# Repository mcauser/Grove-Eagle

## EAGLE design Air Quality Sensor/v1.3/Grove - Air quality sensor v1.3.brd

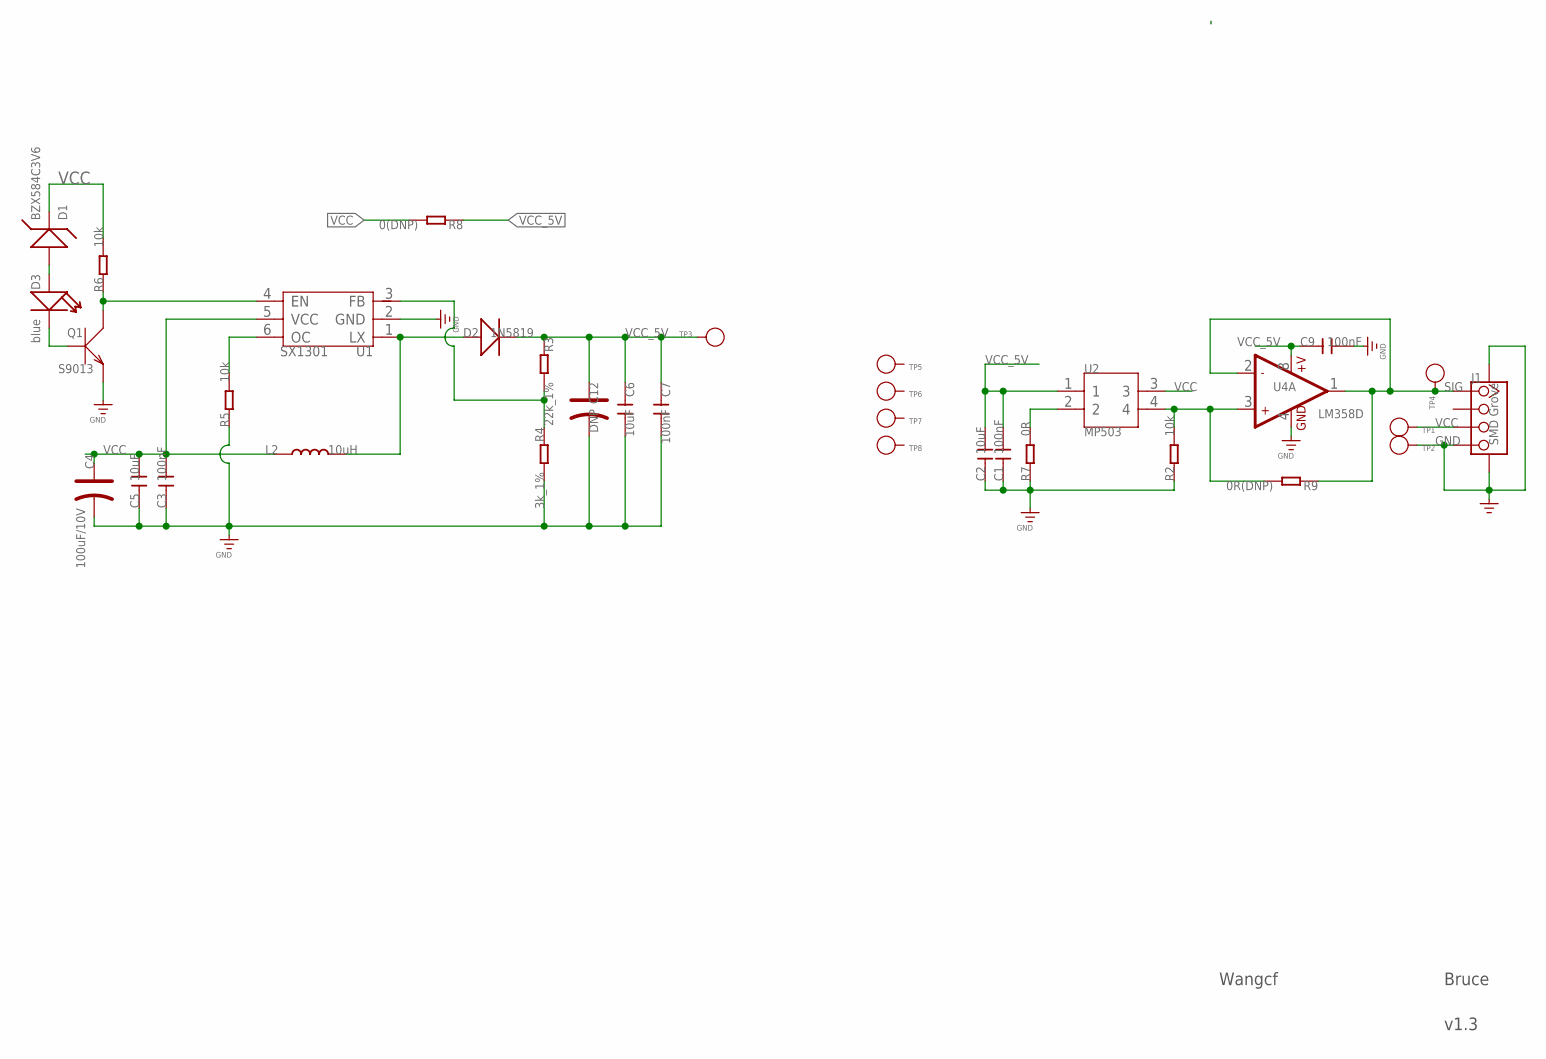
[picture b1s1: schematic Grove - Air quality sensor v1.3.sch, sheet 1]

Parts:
C1, C3, C7, C9: 100nF; C0603
C2, C5, C6: 10uF; C0805
C4: 100uF/10V; AVX-B
C12: DNP; AVX-B
D1: BZX584C3V6; SOD-523
D2: 1N5819; DO-214AC
D3: blue; LED-0603
J1: SMD Grove; 4P-SMD-2.0
L2: 10uH; SD32-4R7MC
Q1: S9013; SOT-23
R2, R5, R6: 10k; R0603
R3: 22k_1%; R0603
R4: 3k_1%; R0603
R7: 0R; R0603
R8: 0(DNP); R0603
R9: 0R(DNP); R0603
TP1, TP2, TP3, TP4, TP5, TP6, TP7, TP8: PAD-TEST-POINT'4545'; TP_4545
U1: SX1301; SOT23-6L
U2: MP503; 4P_3.1_9.4*9.4*17MM
U4: LM358D; SO08

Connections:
EN: Q1.3 (C), R6.1, U1.4 (EN)
GND: C1.1, C2.1, C3.1, C4.-, C5.1, C6.2, C7.2, C9.2, C12.-, J1.4, J1.SS1, J1.SS2, Q1.2 (E), R2.1, R4.2, R5.1, R7.1, TP2.T, U1.2 (GND), U4.4 (GND)
unnamed: R5.2, U1.6 (OC)
unnamed: D1.+, D3.+
unnamed: D2.1 (+), L2.2, U1.1 (LX)
unnamed: D3.-, Q1.1 (B)
unnamed: R7.2, U2.2
unnamed: R3.2, R4.1, U1.3 (FB)
unnamed: R2.2, R9.2, U2.4, U4.3 (+IN1)
SIG: J1.1, R9.1, TP4.T, U4.1 (OUT1), U4.2 (-IN1)
VCC: C3.2, C4.+, C5.2, D1.-, J1.3, L2.1, R6.2, R8.2, TP1.T, U1.5 (VCC), U2.3
VCC_5V: C1.2, C2.2, C6.1, C7.1, C9.1, C12.+, D2.2 (-), R3.1, R8.1, TP3.T, U2.1, U4.8 (+V)

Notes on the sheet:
Wangcf
v1.3
Bruce

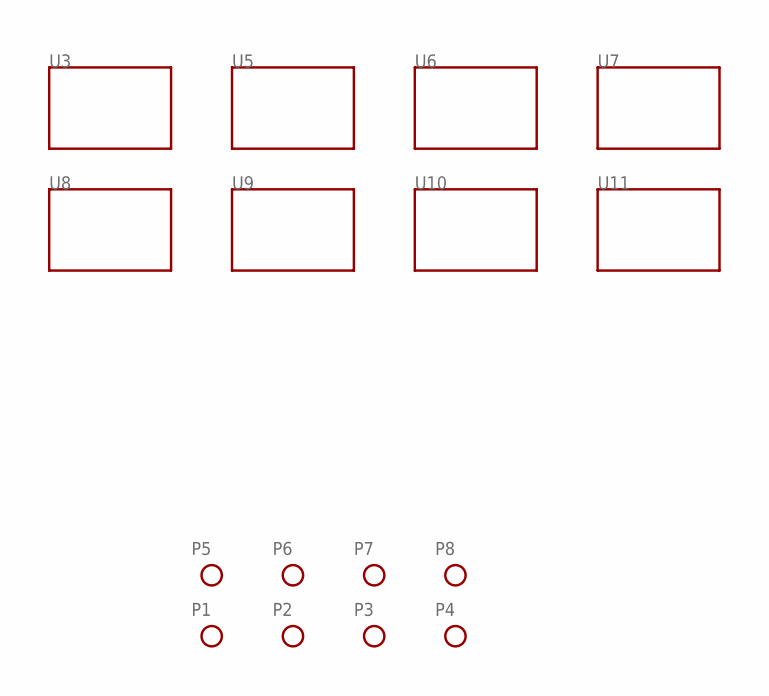
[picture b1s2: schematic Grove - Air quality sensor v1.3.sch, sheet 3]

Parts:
P1, P2, P3, P4, P5, P6, P7, P8: PAD-MARK; ROUND-MARK-1.0
U3, U5, U6, U7, U8, U9, U10, U11: TWIG'2U'; GROVE-TEST-PLATFORM

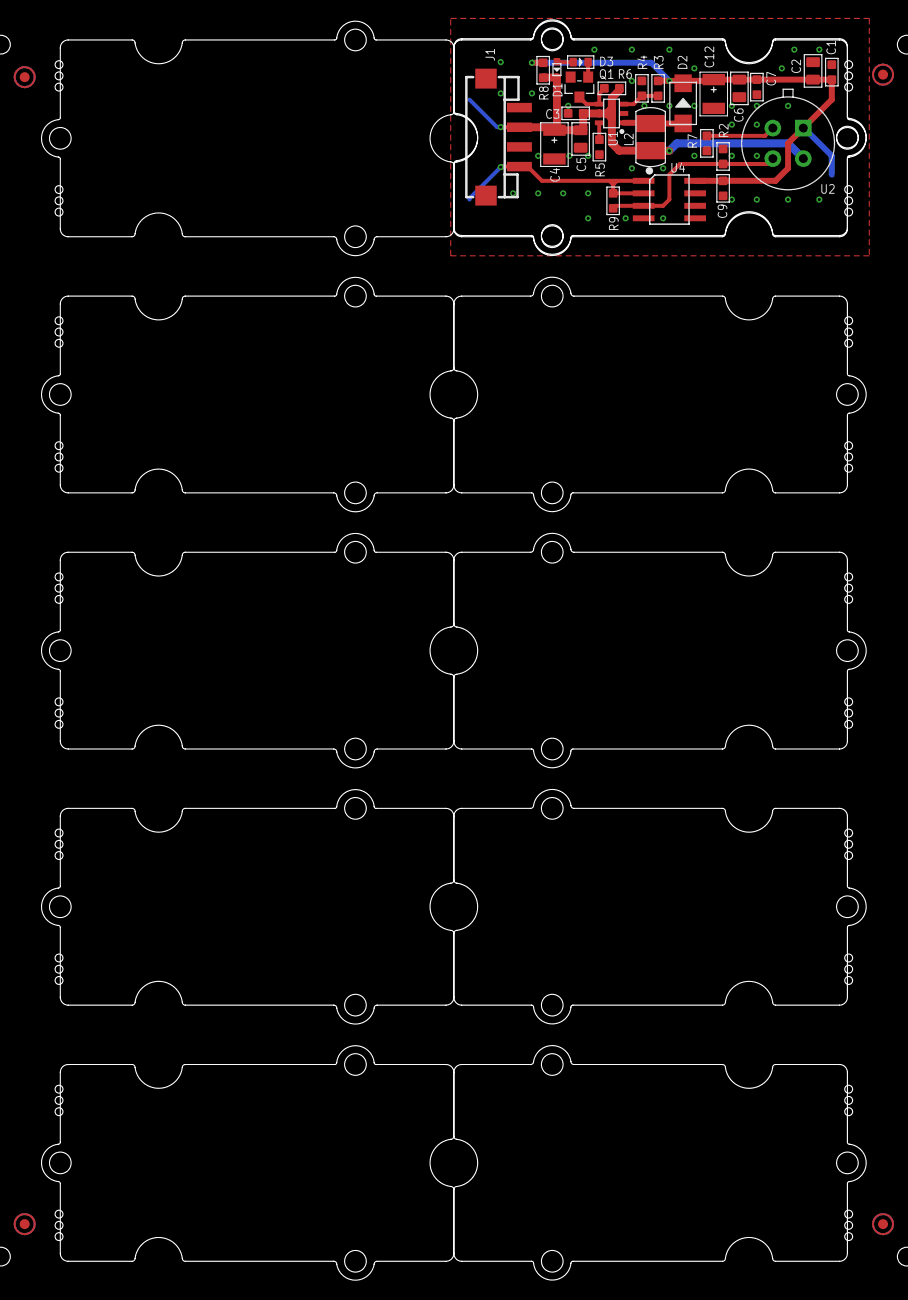
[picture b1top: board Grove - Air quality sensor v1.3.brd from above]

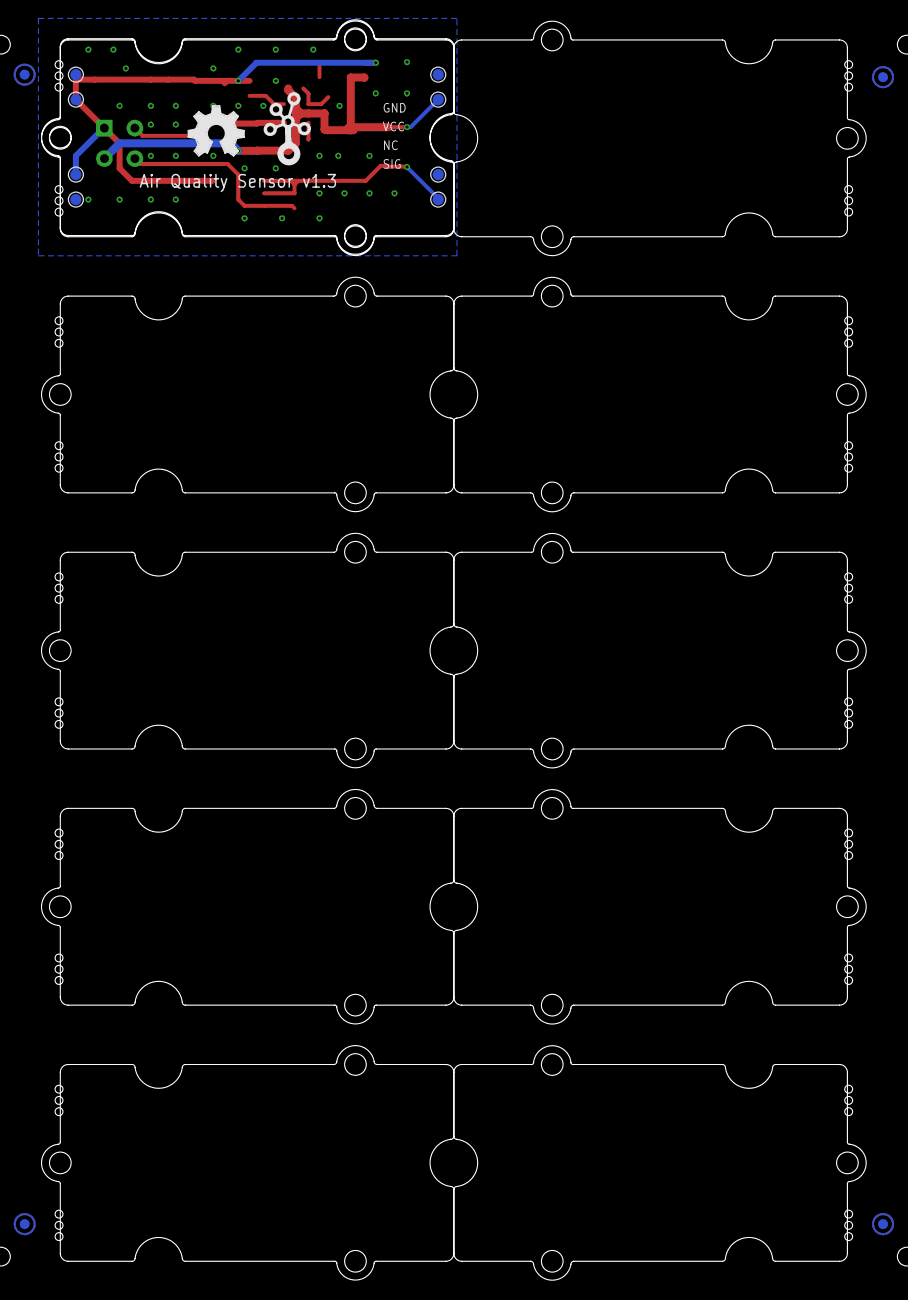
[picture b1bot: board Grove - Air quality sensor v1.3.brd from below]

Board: 2 copper layers, 83.8 x 128.1 mm, 55 parts (14 on the bottom side), 12 nets.

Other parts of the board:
U12, U13: GROVE-TEST-PLATFORM
U$6: GROVE-TEST-PLATFORM
U$7: OSHW_FILLX200_NOTEXT
U$8: TWIGLOGO

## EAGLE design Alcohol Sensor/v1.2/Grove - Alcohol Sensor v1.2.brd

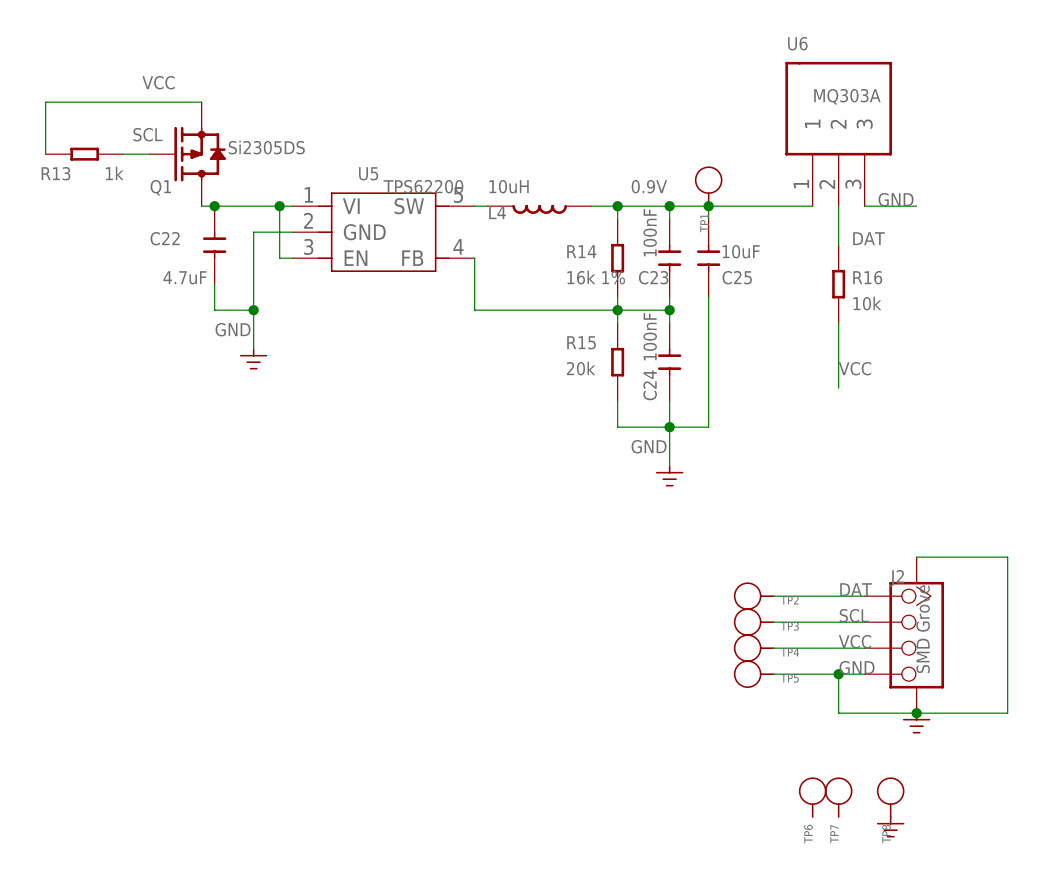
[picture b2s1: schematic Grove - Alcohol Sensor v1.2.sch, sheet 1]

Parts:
C22: 4.7uF; C0805
C23, C24: 100nF; C0603
C25: 10uF; C0805
J2: SMD Grove; 4P-SMD-2.0
L4: 10uH; PIO73
Q1: Si2305DS; SOT23
R13: 1k; R0603
R14: 16k 1%; R0603
R15: 20k; R0603
R16: 10k; R0603
TP1, TP2, TP3, TP4, TP5, TP6, TP7, TP8: PAD-TEST-POINT'4545'; TP_4545
U5: TPS62200; SOT23-5
U6: MQ303A

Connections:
0.9V: C23.2, C25.2, L4.2, R14.1, TP1.T, U6.1
DAT: J2.1, R16.1, TP2.T, U6.2
GND: C22.2, C24.1, C25.1, J2.4, J2.SS1, J2.SS2, R15.2, TP5.T, TP8.T, U5.2 (GND), U6.3
unnamed: C22.1, Q1.3 (D), U5.1 (VI), U5.3 (EN)
unnamed: L4.1, U5.5 (SW)
unnamed: C23.1, C24.2, R14.2, R15.1, U5.4 (FB)
SCL: J2.2, Q1.1 (G), R13.1, TP3.T
VCC: J2.3, Q1.2 (S), R13.2, R16.2, TP4.T

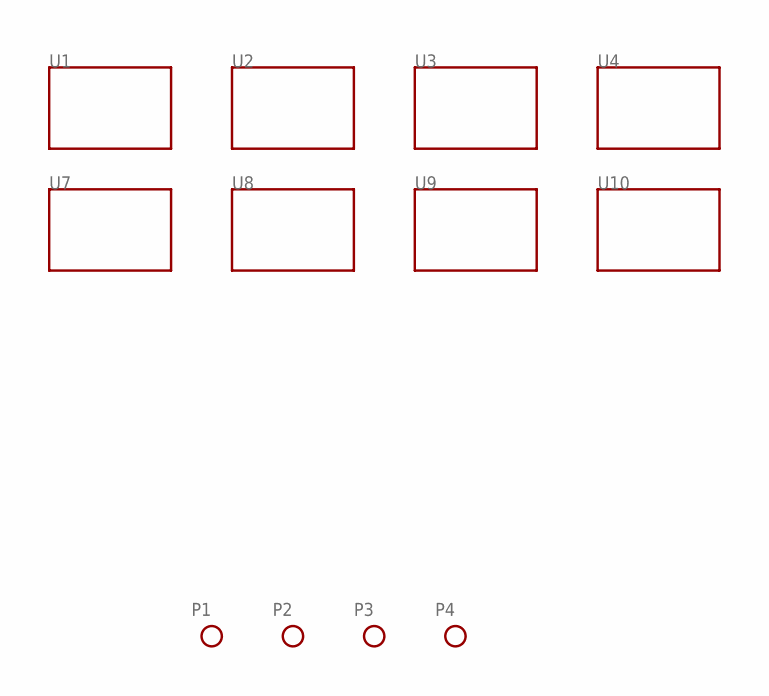
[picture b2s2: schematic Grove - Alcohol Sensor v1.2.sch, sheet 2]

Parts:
P1, P2, P3, P4: PAD-MARK; ROUND-MARK-1.0
U1, U2, U3, U4, U7, U8, U9, U10: TWIG'2U'; GROVE-TEST-PLATFORM

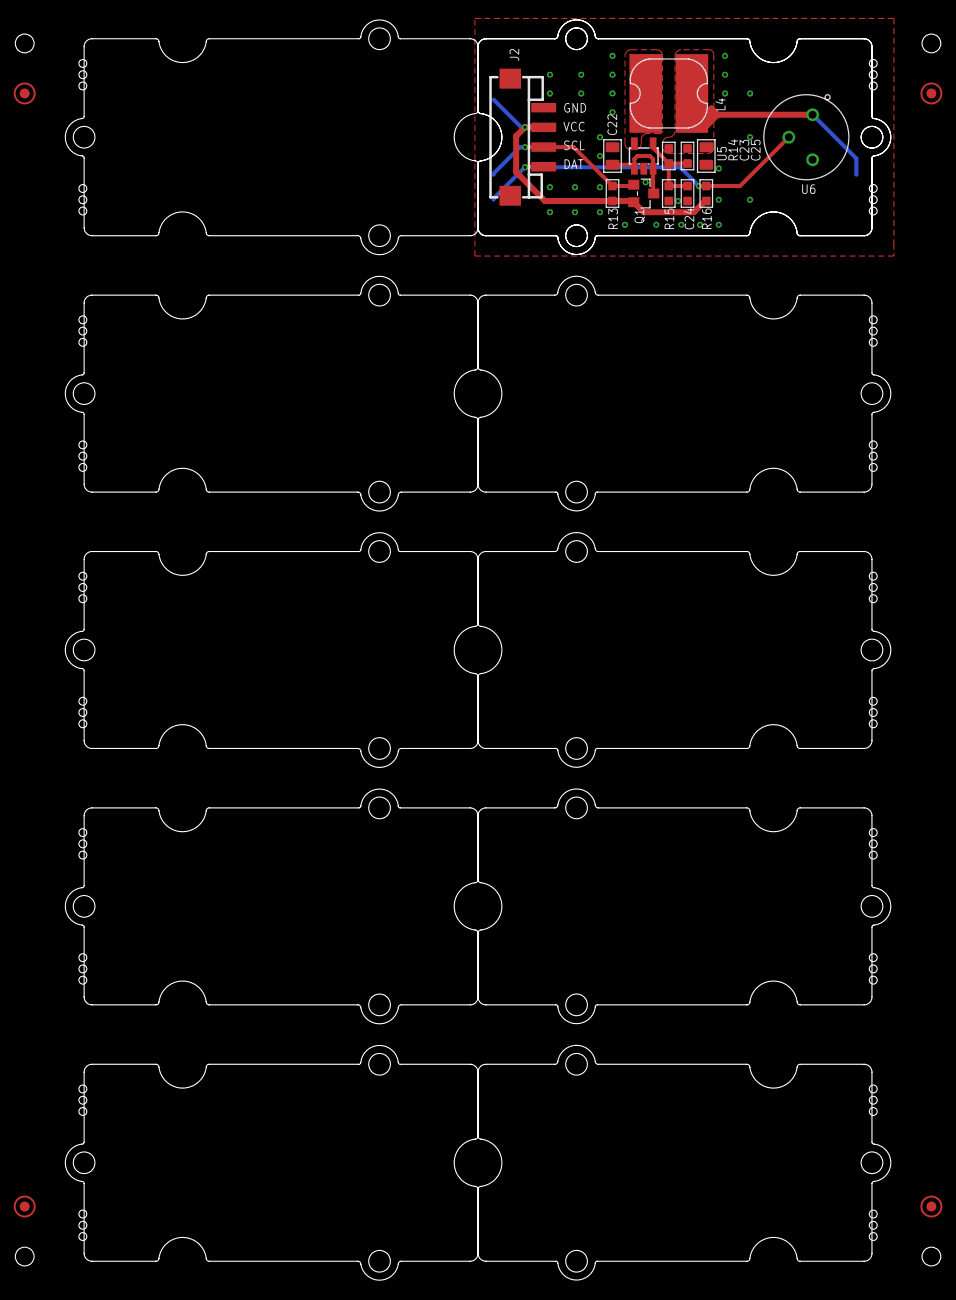
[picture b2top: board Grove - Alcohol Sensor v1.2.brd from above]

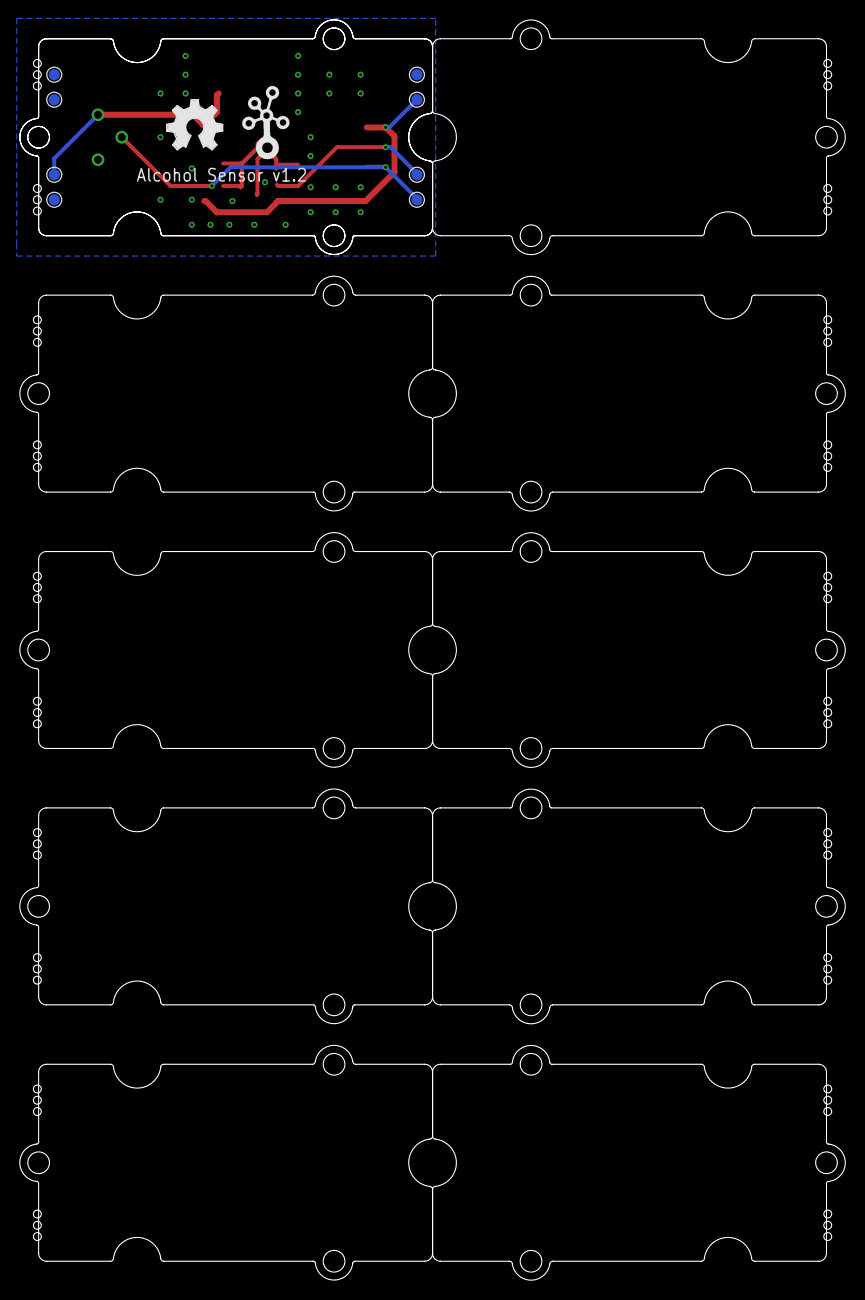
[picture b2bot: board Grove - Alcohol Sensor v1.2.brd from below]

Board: 2 copper layers, 83.8 x 128.0 mm, 38 parts (10 on the bottom side), 8 nets.

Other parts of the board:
U11, U12: GROVE-TEST-PLATFORM
U$2: GROVE-2CONNECTOR-SMD
U$7: OSHW_FILLX200_NOTEXT
U$8: TWIGLOGO

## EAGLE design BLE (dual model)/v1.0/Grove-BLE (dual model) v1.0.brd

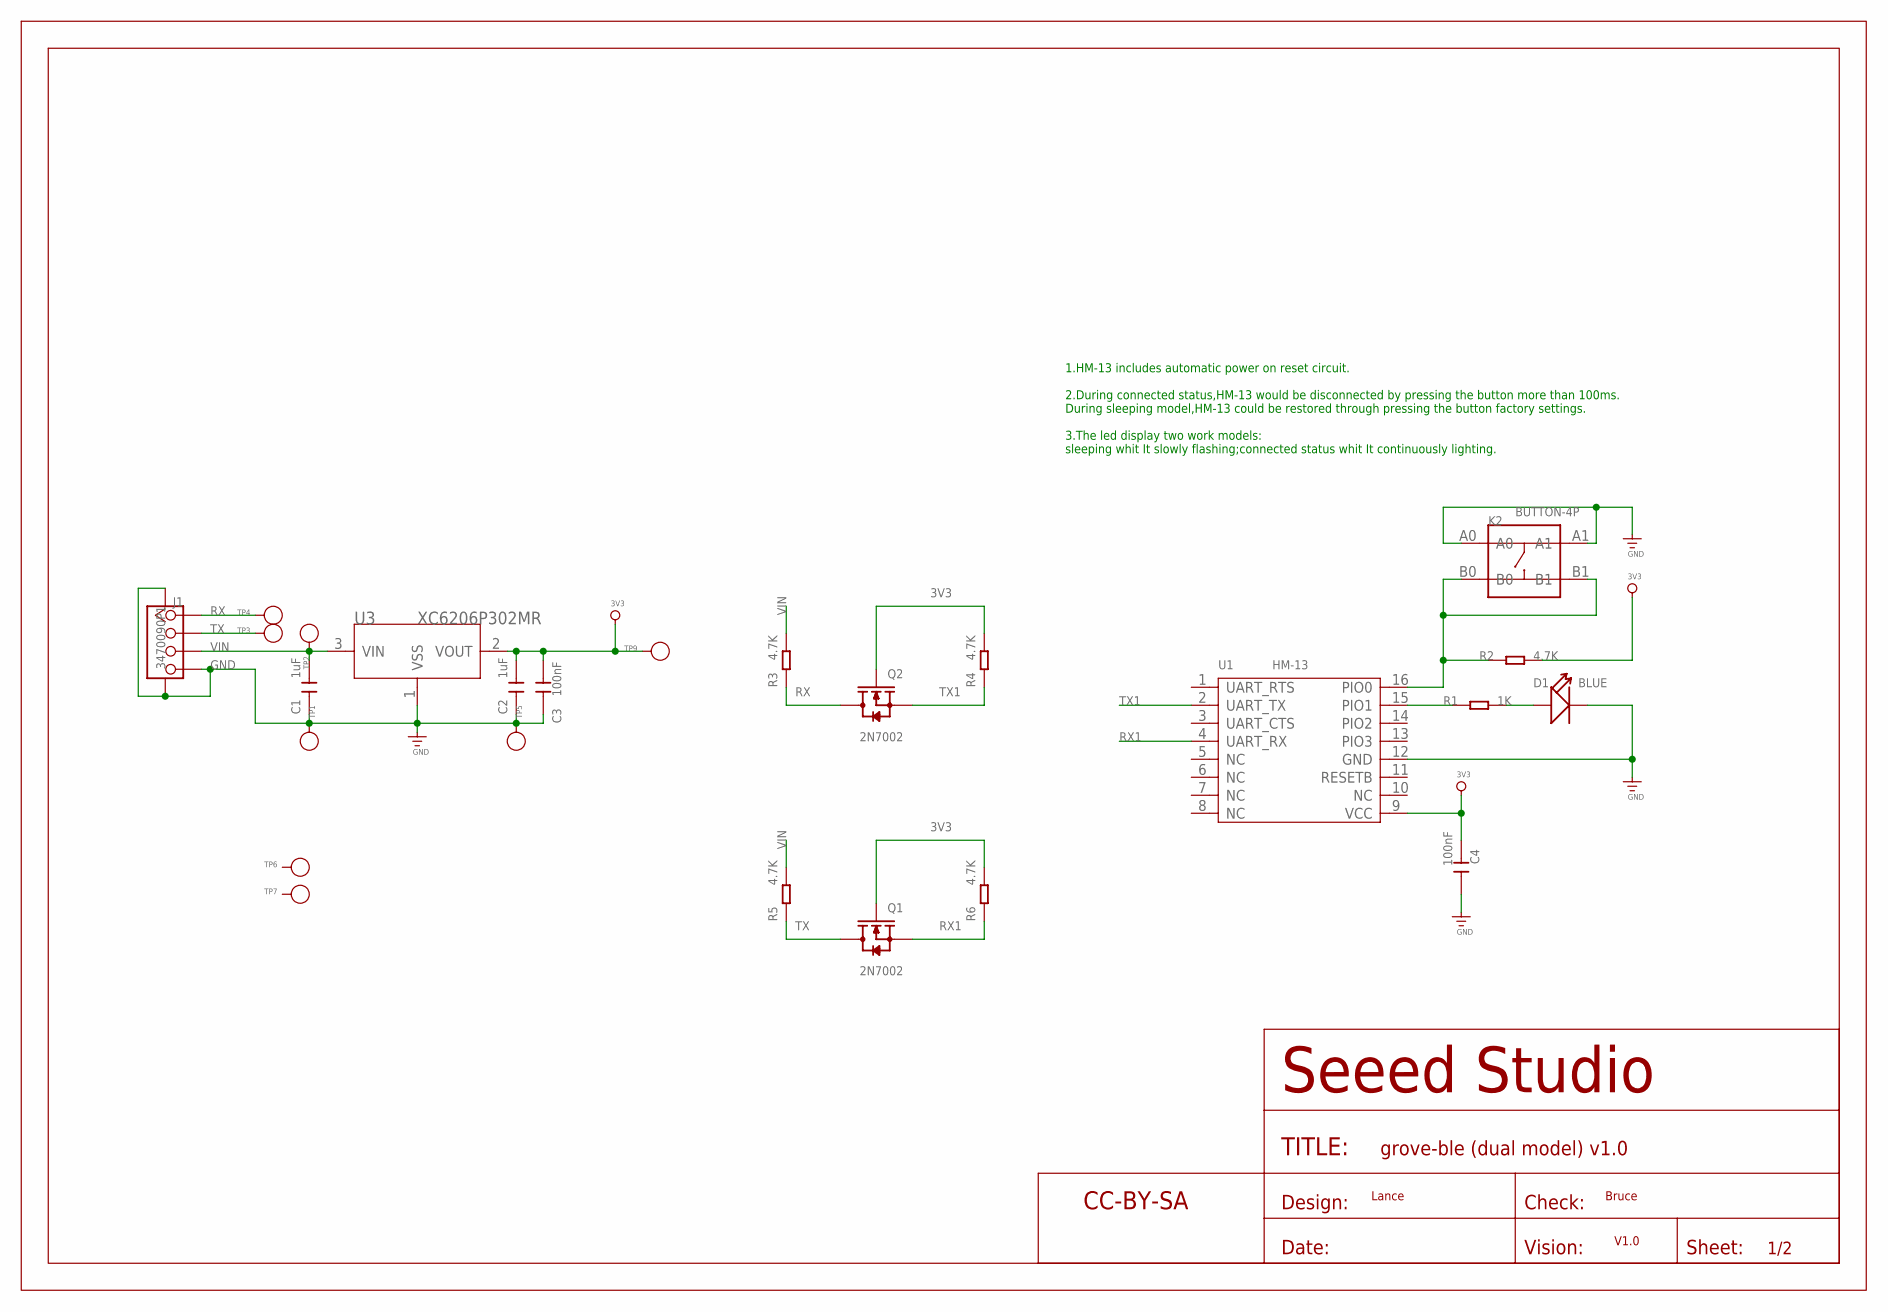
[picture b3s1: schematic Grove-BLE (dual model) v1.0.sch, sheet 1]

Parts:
C1, C2: 1uF; C0603
C3, C4: 100nF; C0603
D1: BLUE; LED-0603
J1: 3470090P1; 4P-SMD-2.0
K2: BUTTON-4P; 4P-SMD-L3.35*W3.35*H1.5MM
Q1, Q2: 2N7002; SOT23
R1: 1K; R0603
R2, R3, R4, R5, R6: 4.7K; R0603
TP1: GND; TP_4545
TP2: VIN; TP_4545
TP3: RX; TP_4545
TP4: TX; TP_4545
TP5, TP6, TP7: PAD-TEST-POINT'4545'; TP_4545
TP9: 3V3; TP_4545
U1: HM-13; 16P-L18.5*W13.5*H2.3MM
U3: XC6206P302MR; SOT23
U$1: SEEEDSTUDIO-OPEN-SCH-FRAME; SEEEDSTUDIO-PCB-FRAME

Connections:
3V3: C2.2, C3.2, C4.1, Q1.1 (G), Q2.1 (G), R2.2, R4.2, R6.2, TP9.T, U1.9 (VCC), U3.2 (VOUT)
GND: C1.1, C2.1, C3.1, C4.2, D1.-, J1.4, J1.SS1, J1.SS2, K2.A0, K2.A1, TP1.T, TP5.T, U1.12 (GND), U3.1 (VSS)
unnamed: R1.1, U1.15 (PIO1)
unnamed: D1.+, R1.2
unnamed: K2.B0, K2.B1, R2.1, U1.16 (PIO0)
RX: J1.1, Q2.3 (D), R3.1, TP4.T
RX1: Q1.2 (S), R6.1, U1.4 (UART_RX)
TX: J1.2, Q1.3 (D), R5.1, TP3.T
TX1: Q2.2 (S), R4.1, U1.2 (UART_TX)
VIN: C1.2, J1.3, R3.2, R5.2, TP2.T, U3.3 (VIN)

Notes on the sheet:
1.HM-13 includes automatic power on reset circuit. 2.During connected status,HM-13 would be disconnected by pressing the button more than 100ms. During sleeping model,HM-13 could be restored through pressing the button factory settings. 3.The led display two work models: sleeping whit It slowly fla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
Lance
Bruce
V1.0

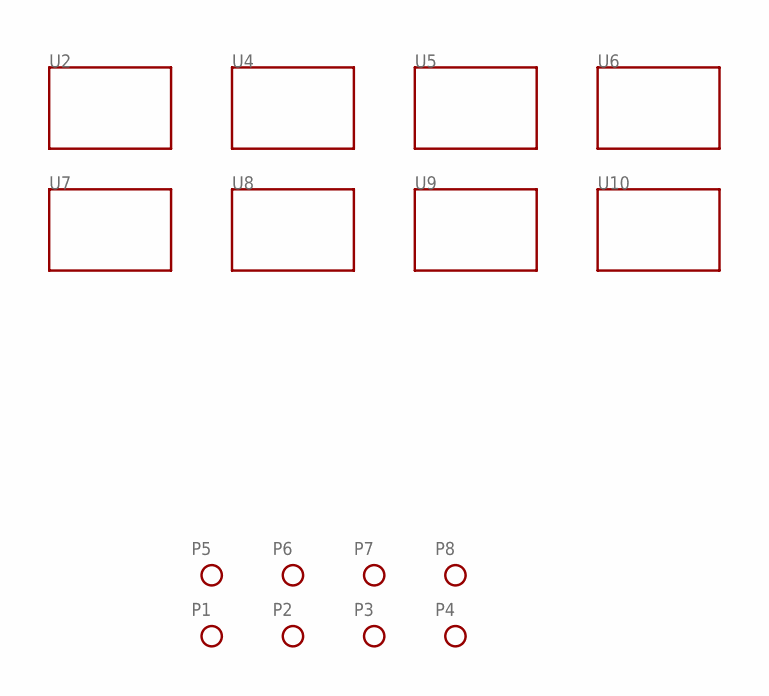
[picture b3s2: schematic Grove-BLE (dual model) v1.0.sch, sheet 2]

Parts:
P1, P2, P3, P4, P5, P6, P7, P8: PAD-MARK; ROUND-MARK-1.0
U2, U4, U5, U6, U7, U8, U9, U10: TWIG'2U'; GROVE-TEST-PLATFORM

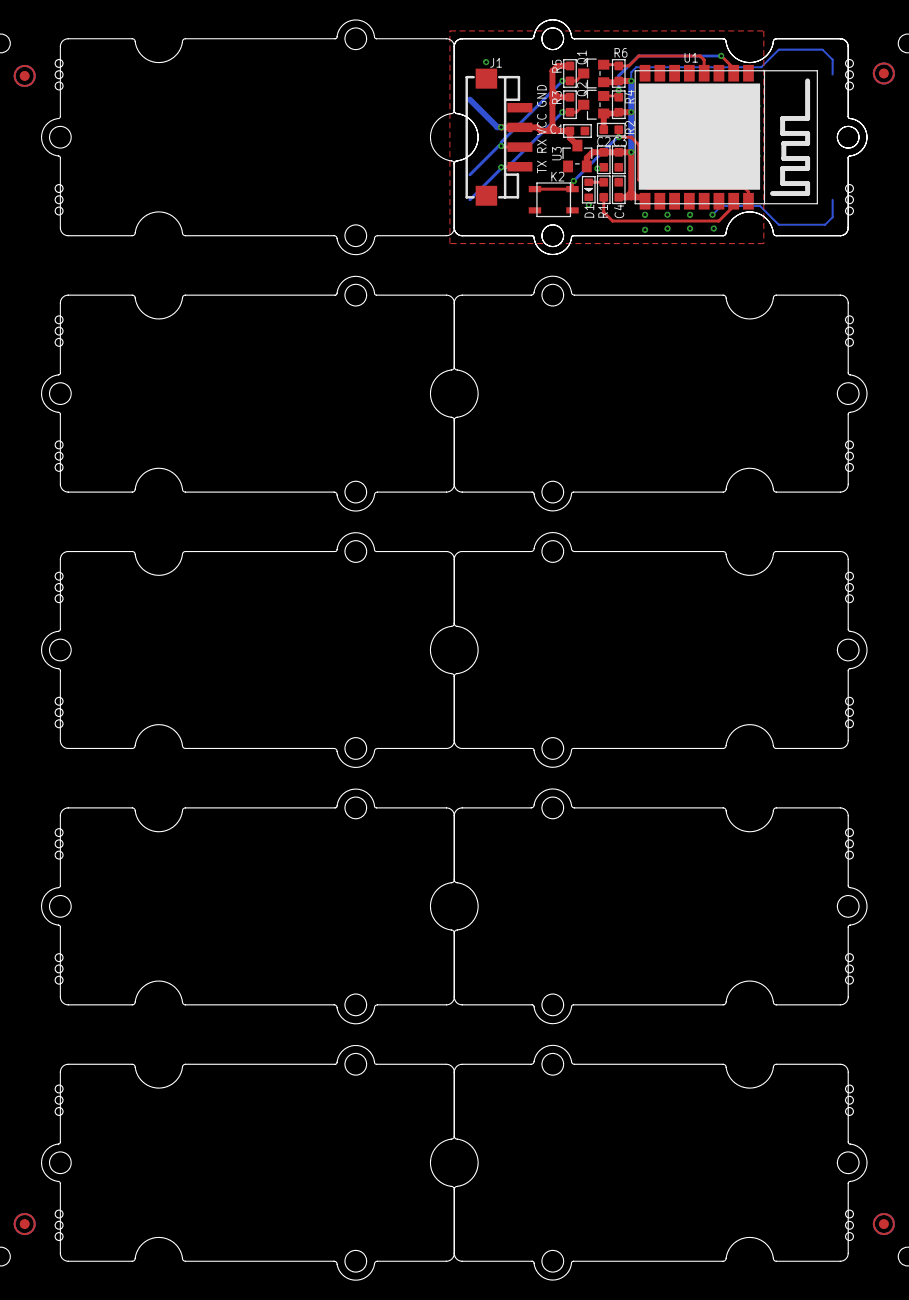
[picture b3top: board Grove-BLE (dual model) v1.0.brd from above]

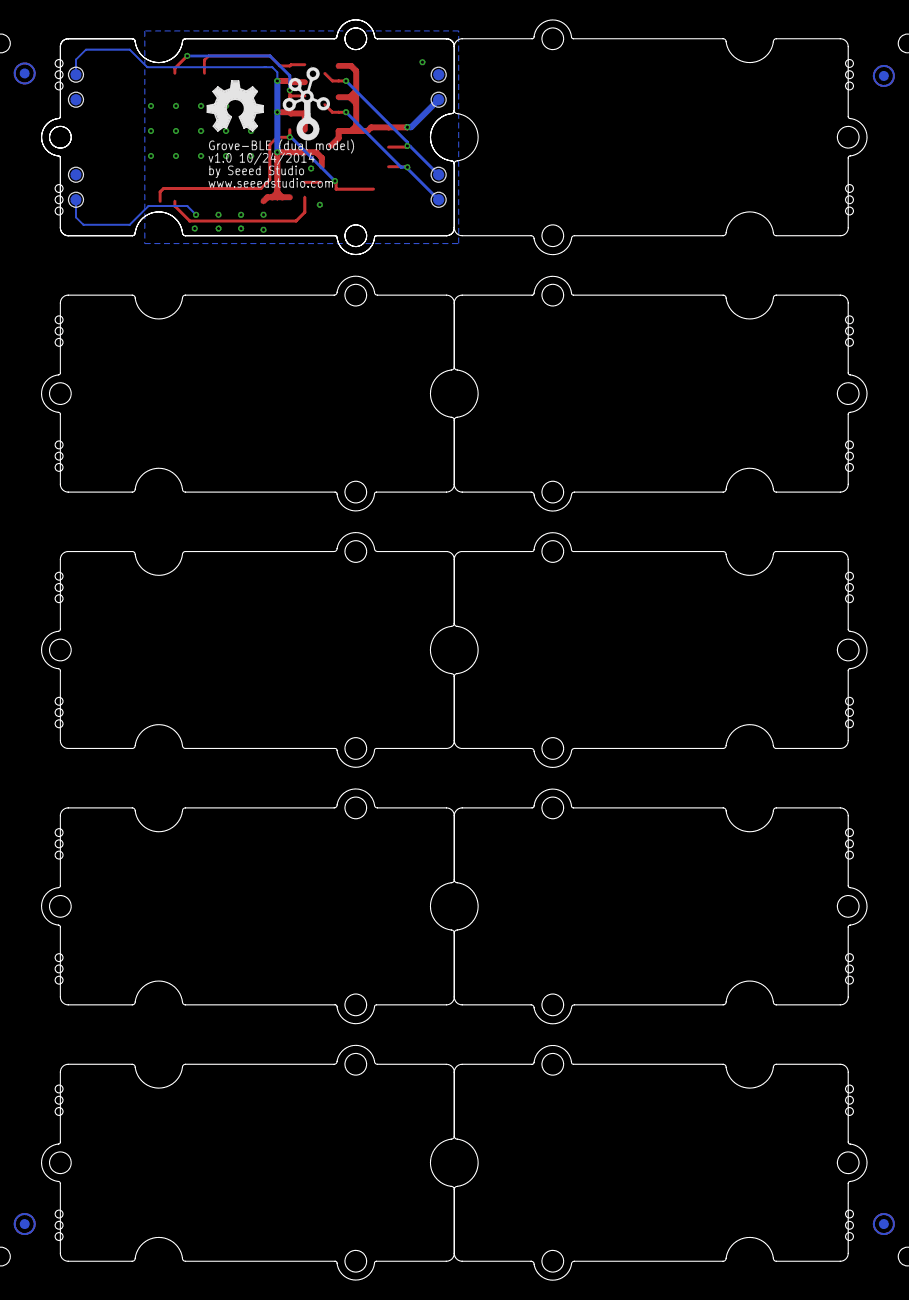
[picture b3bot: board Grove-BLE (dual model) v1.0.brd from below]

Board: 2 copper layers, 83.8 x 128.0 mm, 47 parts (14 on the bottom side), 10 nets.

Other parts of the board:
U11, U12: GROVE-TEST-PLATFORM@1
U$5: GROVE-1*2-TEST-PLATFORM
U$6: OSHW_FILLX200_NOTEXT
U$7: TWIGLOGO

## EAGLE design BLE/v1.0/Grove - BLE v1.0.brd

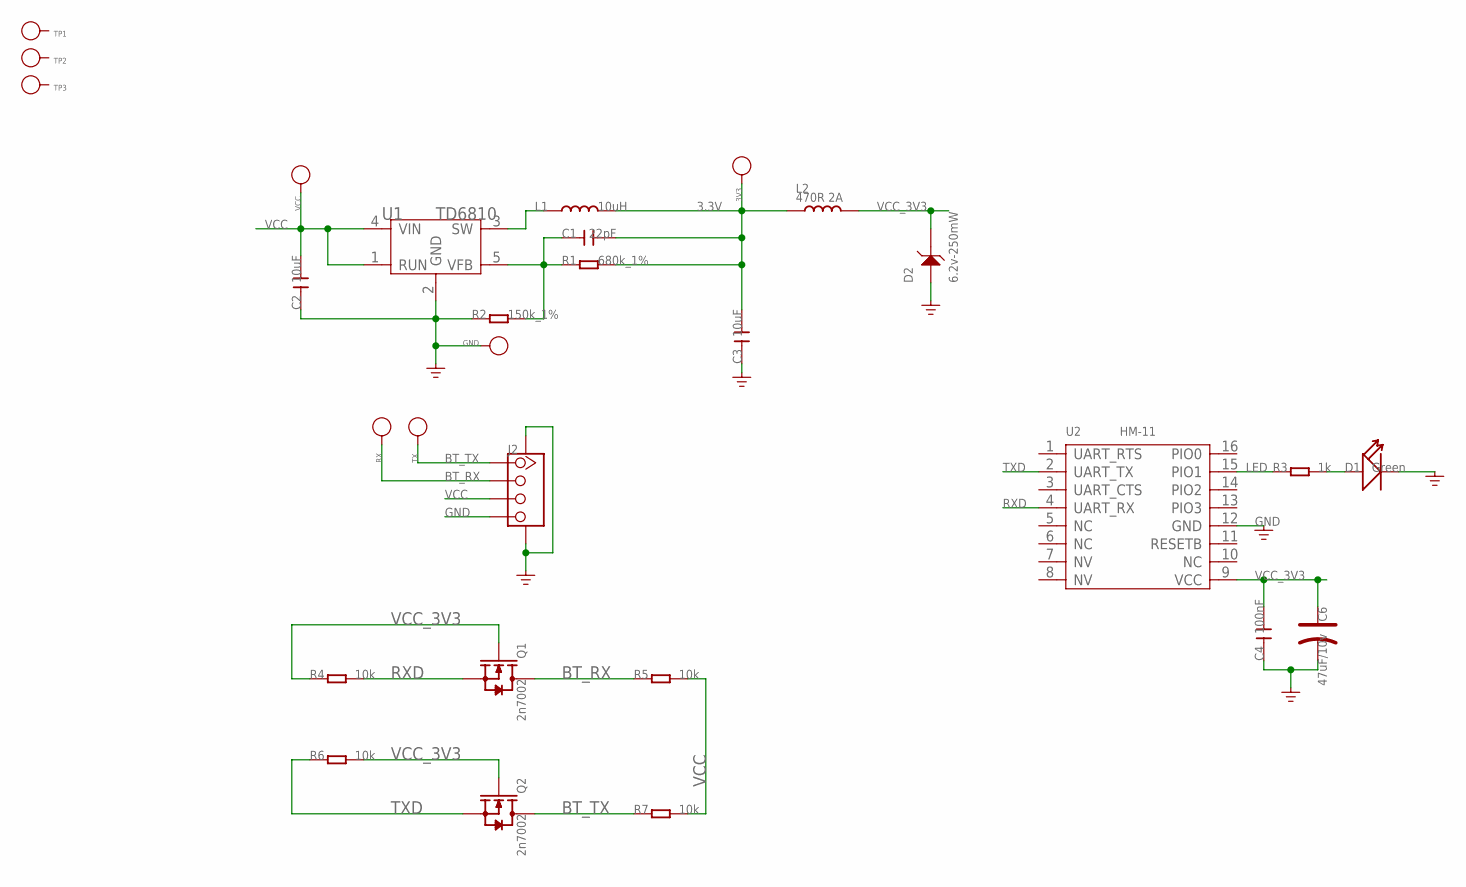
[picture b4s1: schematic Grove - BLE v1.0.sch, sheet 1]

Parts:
3V3: PAD-TEST-POINT'4545'; TP_4545
C1: 22pF; C0603
C2, C3: 10uF; C0805
C4: 100nF; C0603
C6: 47uF/10v; AVX-B
D1: Green; LED-0603
D2: 6.2v-250mW; SOD123-2.7X1.6
GND: PAD-TEST-POINT'4545'; TP_4545
J2: TWIG-4P-2.0-SMD-FEMALE-REINFORCE'DD'; 4P-SMD-2.0
L1: 10uH; 1813
L2: 470R 2A; L0805
Q1, Q2: 2n7002; SOT23
R1: 680k_1%; 0603@1
R2: 150k_1%; 0603@1
R3: 1k; R0603
R4, R5, R6, R7: 10k; R0603
RX: PAD-TEST-POINT'4545'; TP_4545
TP1, TP2, TP3: PAD-TEST-POINT'4545'; TP_4545
TX: PAD-TEST-POINT'4545'; TP_4545
U1: TD6810; SOT23-5
U2: HM-11; 16P-18.5X13.5X0.8
VCC: PAD-TEST-POINT'4545'; TP_4545

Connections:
3.3V: 3V3.T, C1.2, C3.2, L1.2, L2.1, R1.2
BT_RX: J2.2, Q1.3 (D), R5.1, RX.T
BT_TX: J2.1, Q2.3 (D), R7.1, TX.T
GND: C2.1, C3.1, C4.1, C6.-, D1.-, D2.1, GND.T, J2.4, J2.SS1, J2.SS2, R2.1, U1.2 (GND), U2.12 (GND)
LED: R3.1, U2.15 (PIO1)
unnamed: D1.+, R3.2
unnamed: C1.1, R1.1, R2.2, U1.5 (VFB)
unnamed: L1.1, U1.3 (SW)
RXD: Q1.2 (S), R4.2, U2.4 (UART_RX)
TXD: Q2.2 (S), R6.1, U2.2 (UART_TX)
VCC: C2.2, J2.3, R5.2, R7.2, U1.1 (RUN), U1.4 (VIN), VCC.T
VCC_3V3: C4.2, C6.+, D2.2, L2.2, Q1.1 (G), Q2.1 (G), R4.1, R6.2, U2.9 (VCC)

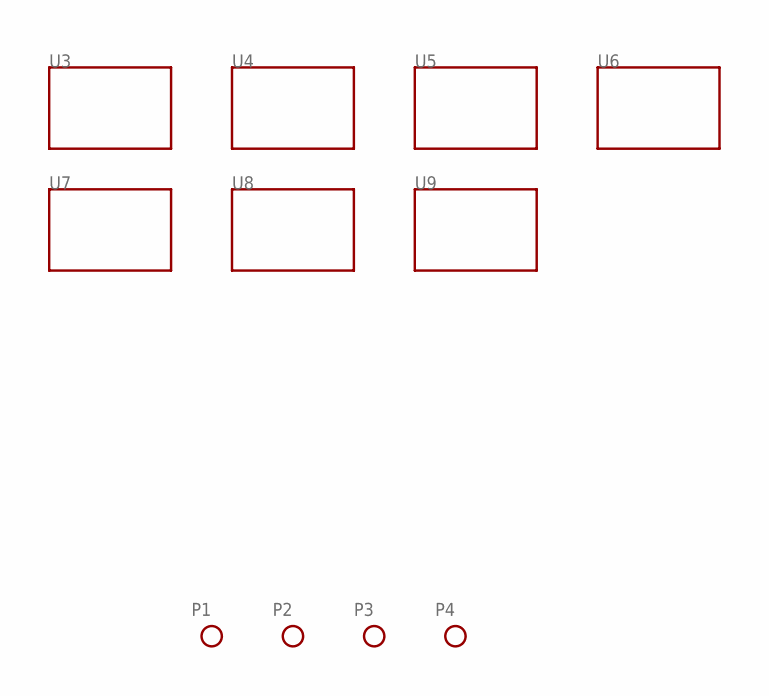
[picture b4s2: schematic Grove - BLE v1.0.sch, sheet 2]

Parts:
P1, P2, P3, P4: PAD-MARK; ROUND-MARK-1.0
U3, U4, U5, U6, U7, U8, U9: TWIG'2U'; GROVE-TEST-PLATFORM

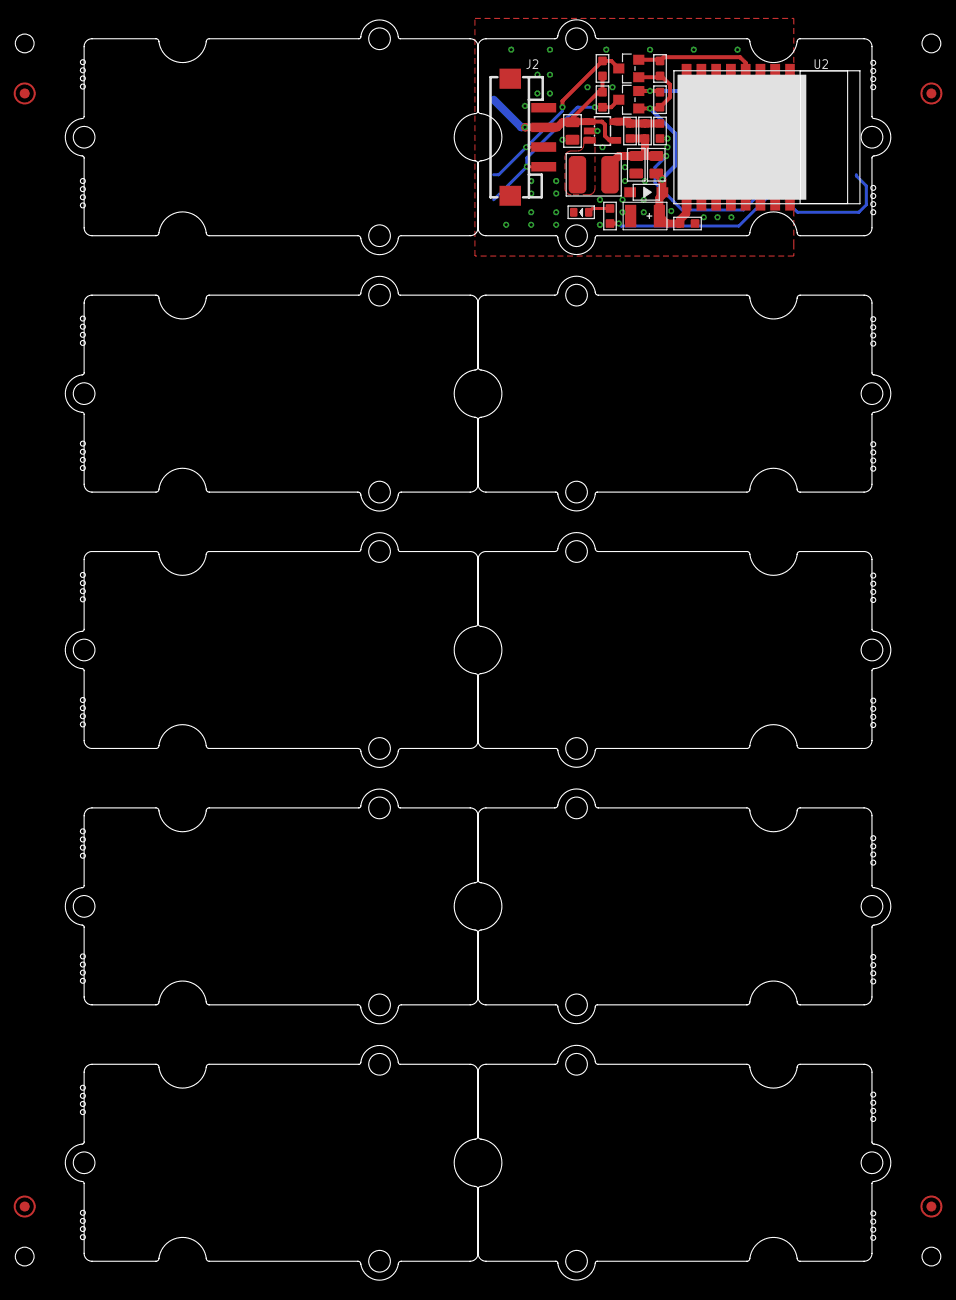
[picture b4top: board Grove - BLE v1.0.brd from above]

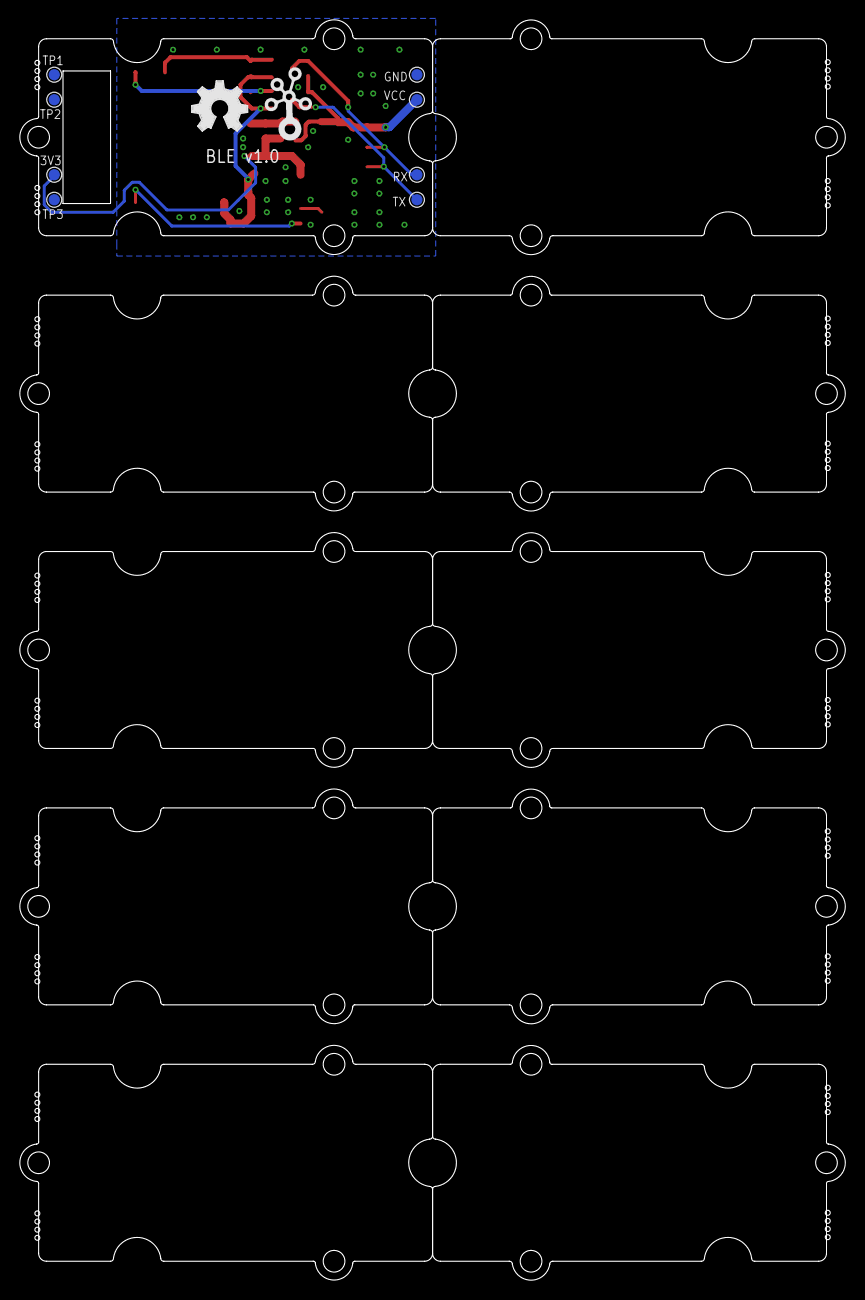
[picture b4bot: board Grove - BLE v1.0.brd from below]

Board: 2 copper layers, 83.8 x 128.0 mm, 45 parts (10 on the bottom side), 12 nets.

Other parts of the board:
U11, U12: GROVE-TEST-PLATFORM
U$6: GROVE-2CONNECTOR
U$8: OSHW_FILLX200_NOTEXT
U$9: TWIGLOGO

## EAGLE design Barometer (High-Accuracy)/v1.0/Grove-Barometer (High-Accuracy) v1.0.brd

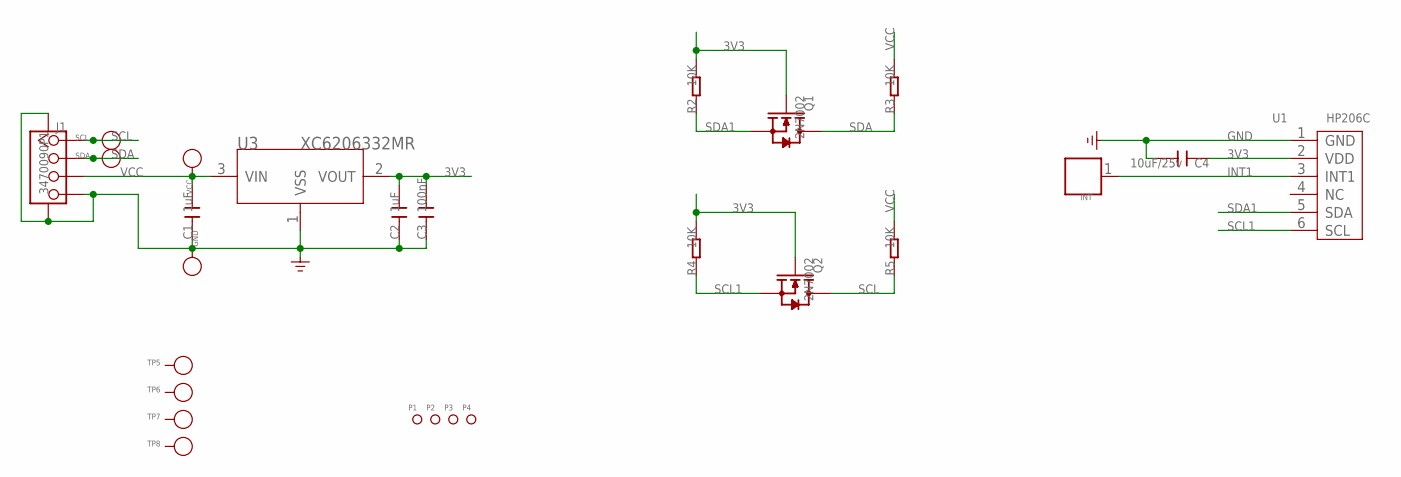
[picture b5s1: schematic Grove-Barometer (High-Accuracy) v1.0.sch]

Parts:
C1, C2: 1uF; C0603
C3: 100nF; C0603
C4: 10uF/25v; C0805
GND: PAD-TEST-POINT'4545'; TP_4545
INT: PAD'60/30'; 1P-65/35MIL
J1: 3470090P1; 4P-SMD-2.0
P1, P2, P3, P4: PAD-MARK; ROUND-MARK-1.0
Q1, Q2: 2N7002; SOT23
R2, R3, R4, R5: 10K; R0603
SCL: PAD-TEST-POINT'4545'; TP_4545
SDA: PAD-TEST-POINT'4545'; TP_4545
TP5, TP6, TP7, TP8: PAD-TEST-POINT'4545'; TP_4545
U1: HP206C; 6P-SMD-6.8X6.2
U3: XC6206332MR; SOT23
VCC: PAD-TEST-POINT'4545'; TP_4545

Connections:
3V3: C2.2, C3.2, C4.1, Q1.1 (G), Q2.1 (G), R2.2, R4.2, U1.2 (VDD), U3.2 (VOUT)
GND: C1.1, C2.1, C3.1, C4.2, GND.T, J1.4, J1.SS1, J1.SS2, U1.1 (GND), U3.1 (VSS)
INT1: INT.1, U1.3 (INT1)
SCL: J1.1, Q2.3 (D), R5.1, SCL.T
SCL1: Q2.2 (S), R4.1, U1.6 (SCL)
SDA: J1.2, Q1.3 (D), R3.1, SDA.T
SDA1: Q1.2 (S), R2.1, U1.5 (SDA)
VCC: C1.2, J1.3, R3.2, R5.2, U3.3 (VIN), VCC.T

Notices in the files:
parts and their libraries:
moudle-new: This work is licensed under the Creative Commons Attribution 4.0 International License.
To view a copy of this license,visit:
http://creativecommons.org/licenses/by-sa/4.0
moudle-new: CC-BY-SA
